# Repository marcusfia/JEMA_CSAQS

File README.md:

# **JEMA SD Project - Citizen Science Air Quality Sensor**
Sponsered by Dr. Jun Wang and the University of Iowa ARROMA Lab

This repository contains all source code used for the project.

If you would like to know more about the project software/hardware or access user guides, please visit the project wiki:

## [Project Wiki](https://github.com/marcusfia/JEMA_CSAQS/wiki)

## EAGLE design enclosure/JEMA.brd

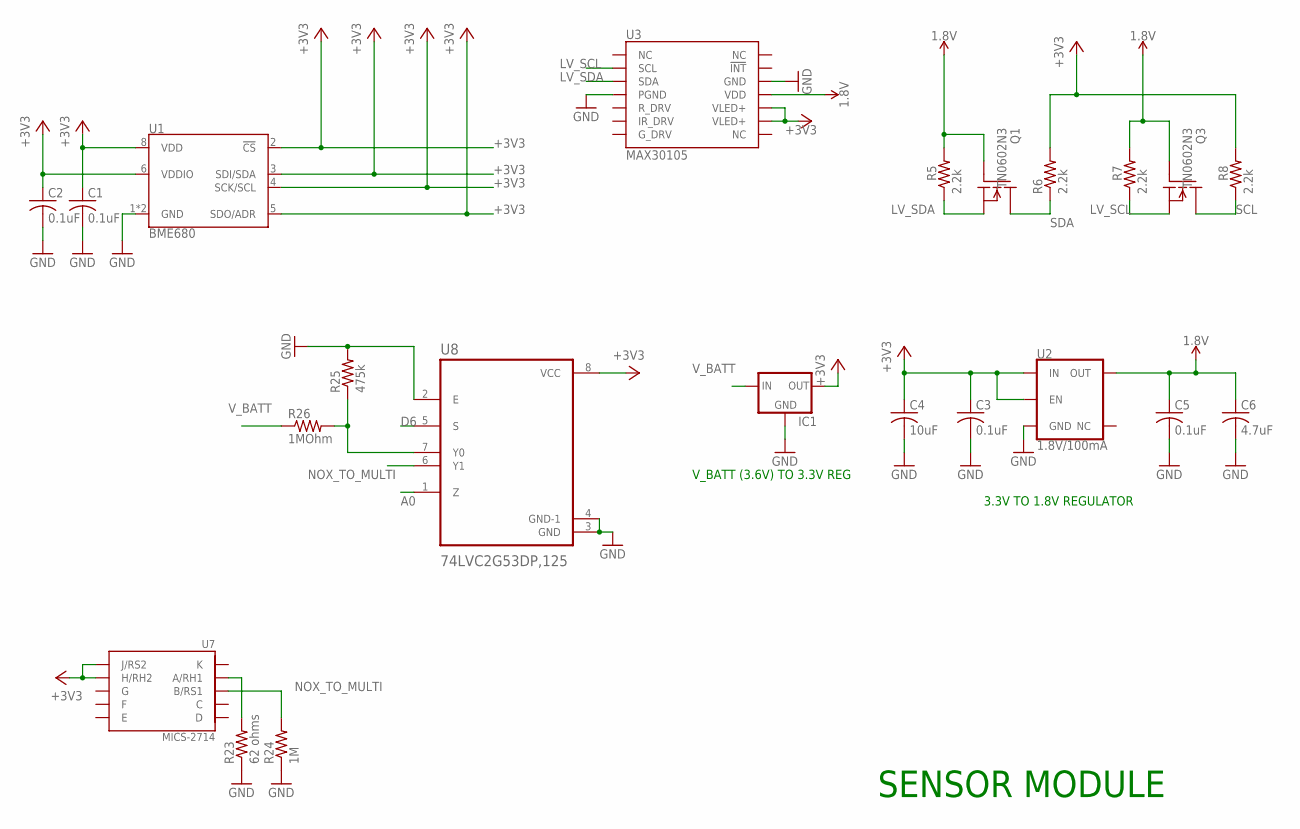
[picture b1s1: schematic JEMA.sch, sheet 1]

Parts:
C1, C2, C3, C5: 0.1uF; C0805
C4: 10uF; C0805
C6: 4.7uF; C0805
IC1: MCP1700TRI; TO92
Q1, Q3: TN0602N3; TO-92
R5, R6, R7, R8: 2.2k; R0805
R23: 62 ohms; M0805
R24: 1M; M0805
R25: 475k; M0805
R26: 1MOhm; M0805
U1: BME680; LGA3.0X3.0
U2: 1.8V/100mA; SC70
U3: MAX30105; OLGA-14
U7: MICS-2714; MICS-SMD10
U8: 74LVC2G53DP,125; SOP65P490X110-8N

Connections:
1.8V: C5.1, C6.1, Q1.2 (G), Q3.2 (G), R5.2, R7.2, U2.5 (OUT), U3.11 (VDD)
+3V3: C1.1, C2.1, C3.1, C4.1, IC1.3 (OUT), R6.2, R8.2, U1.2 (!CS), U1.3 (SDI/SDA), U1.4 (SCK/SCL), U1.5 (SDO/ADR), U1.6 (VDDIO), U1.8 (VDD), U2.1 (IN), U2.3 (EN), U3.9 (VLED+), U3.10 (VLED+), U7.H (H/RH2), U7.J (J/RS2), U8.8 (VCC); also elsewhere on the board
A0: U8.1 (Z); also elsewhere on the board
D6: U8.5 (S); also elsewhere on the board
GND: C1.2, C2.2, C3.2, C4.2, C5.2, C6.2, IC1.1 (GND), R23.1, R24.1, R25.2, U1.1 (GND), U1.7 (GND), U2.2 (GND), U3.4 (PGND), U3.12 (GND), U8.2 (E), U8.3 (GND), U8.4 (GND-1); also elsewhere on the board
LV_SCL: Q3.1 (S), R7.1, U3.2 (SCL)
LV_SDA: Q1.1 (S), R5.1, U3.3 (SDA)
unnamed: R25.1, R26.2, U8.7 (Y0)
unnamed: R23.2, U7.A (A/RH1)
NOX_TO_MULTI: R24.2, U7.B (B/RS1), U8.6 (Y1)
SCL: Q3.3 (D), R8.1; also elsewhere on the board
SDA: Q1.3 (D), R6.1; also elsewhere on the board
V_BATT: IC1.2 (IN), R26.1; also elsewhere on the board

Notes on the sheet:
V_BATT (3.6V) TO 3.3V REG
3.3V TO 1.8V REGULATOR
SENSOR MODULE

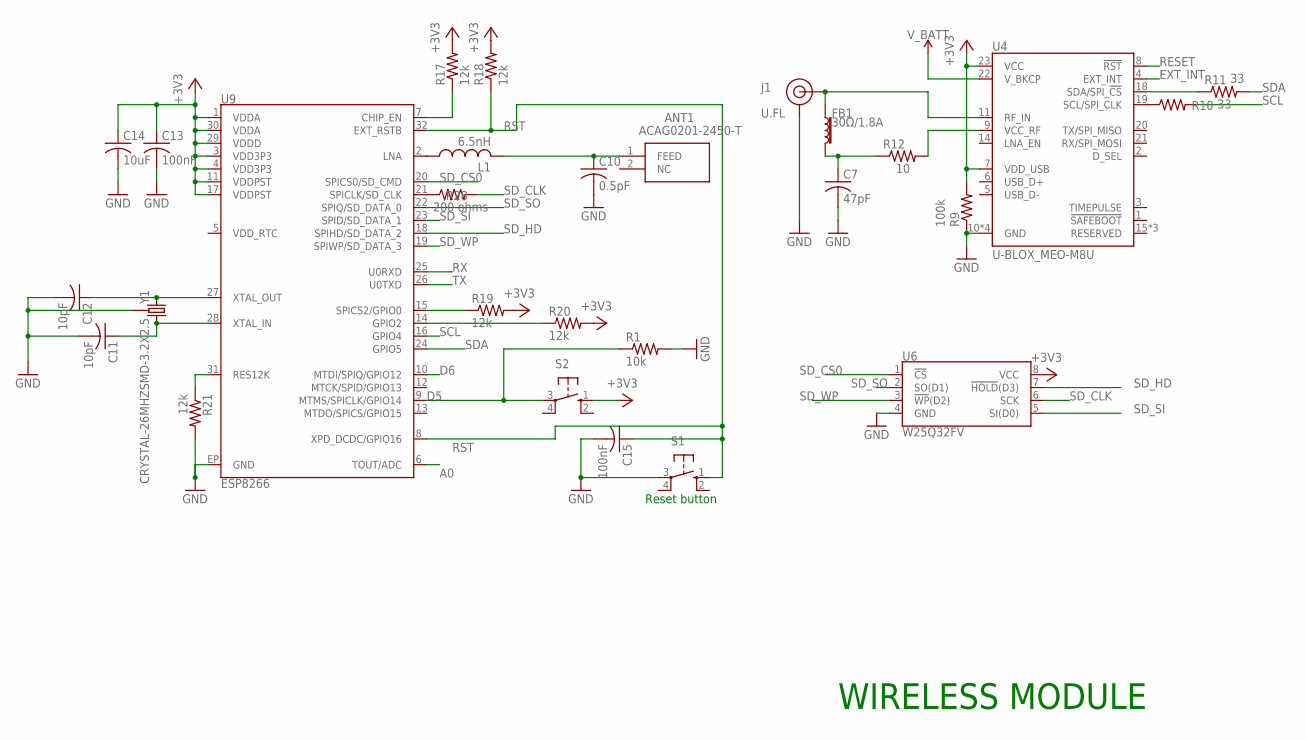
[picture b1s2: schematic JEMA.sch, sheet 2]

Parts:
ANT1: ACAG0201-2450-T; ANTC2012X70N
C7: 47pF; C0805
C10: 0.5pF; C0805
C11, C12: 10pF; C0805
C13, C15: 100nF; C0805
C14: 10uF; C0805
FB1: 30Ω/1.8A; 0603
J1: U.FL
L1: 6.5nH; L3225M
R1: 10k; R0805
R9: 100k; R0805
R10, R11: 33; R0805
R12: 10; R0805
R17, R18, R19, R20, R21: 12k; M0805
R28: 200 ohms; R0805
S1, S2: 10-XX; B3F-10XX
U4: U-BLOX_MEO-M8U; NEO-M9N/M8T/M8U
U6: W25Q32FV; SOIC-8
U9: ESP8266; QFN32-5X5MM
Y1: CRYSTAL-26MHZSMD-3.2X2.5; CRYSTAL-SMD-3.2X2.5MM

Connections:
+3V3: C13.1, C14.1, R9.2, R17.2, R18.2, R19.2, R20.2, S2.1 (S), U4.7 (VDD_USB), U4.23 (VCC), U6.8 (VCC), U9.1 (VDDA), U9.3 (VDD3P3), U9.4 (VDD3P3), U9.11 (VDDPST), U9.17 (VDDPST), U9.29 (VDDD), U9.30 (VDDA); also elsewhere on the board
A0: U9.6 (TOUT/ADC); also elsewhere on the board
D5: R1.1, S2.3, U9.9 (MTMS/SPICLK/GPIO14)
D6: U9.10 (MTDI/SPIQ/GPIO12); also elsewhere on the board
EXT_INT: U4.4 (EXT_INT)
GND: C7.2, C10.2, C11.2, C12.2, C13.2, C14.2, C15.2, J1.1 (GND), J1.2 (GND), R1.2, R9.1, R21.2, S1.3, U4.10 (GND), U4.12 (GND), U4.13 (GND), U4.24 (GND), U6.4 (GND), U9.EP (GND), Y1.2 (GND), Y1.4 (GND); also elsewhere on the board
unnamed: R10.1, U4.19 (SCL/SPI_CLK)
unnamed: R11.1, U4.18 (SDA/SPI_!CS!)
unnamed: C7.1, FB1.2, R12.1
unnamed: R12.2, U4.9 (VCC_RF)
unnamed: R17.1, U9.7 (CHIP_EN)
unnamed: L1.1, U9.2 (LNA)
unnamed: ANT1.1 (FEED), C10.1, L1.2
unnamed: R19.1, U9.15 (SPICS2/GPIO0)
unnamed: R20.1, U9.14 (GPIO2)
unnamed: R21.1, U9.31 (RES12K)
unnamed: C12.1, U9.27 (XTAL_OUT), Y1.1
unnamed: C11.1, U9.28 (XTAL_IN), Y1.3 (2)
unnamed: FB1.1, J1.FEED (SIGNAL), U4.11 (RF_IN)
unnamed: R28.1, U9.21 (SPICLK/SD_CLK)
RESET: U4.8 (!RST)
RST: C15.1, R18.1, S1.1 (S), U9.8 (XPD_DCDC/GPIO16), U9.32 (EXT_RSTB)
RX: U9.25 (U0RXD)
SCL: R10.2, U9.16 (GPIO4); also elsewhere on the board
SDA: R11.2, U9.24 (GPIO5); also elsewhere on the board
SD_CLK: R28.2, U6.6 (SCK)
SD_CS0: U6.1 (!CS!), U9.20 (SPICS0/SD_CMD)
SD_HD: U6.7 (!HOLD!(D3)), U9.18 (SPIHD/SD_DATA_2)
SD_SI: U6.5 (SI(D0)), U9.23 (SPID/SD_DATA_1)
SD_SO: U6.2 (SO(D1)), U9.22 (SPIQ/SD_DATA_0)
SD_WP: U6.3 (!WP!(D2)), U9.19 (SPIWP/SD_DATA_3)
TX: U9.26 (U0TXD)
V_BATT: U4.22 (V_BKCP); also elsewhere on the board

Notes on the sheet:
Reset button
WIRELESS MODULE

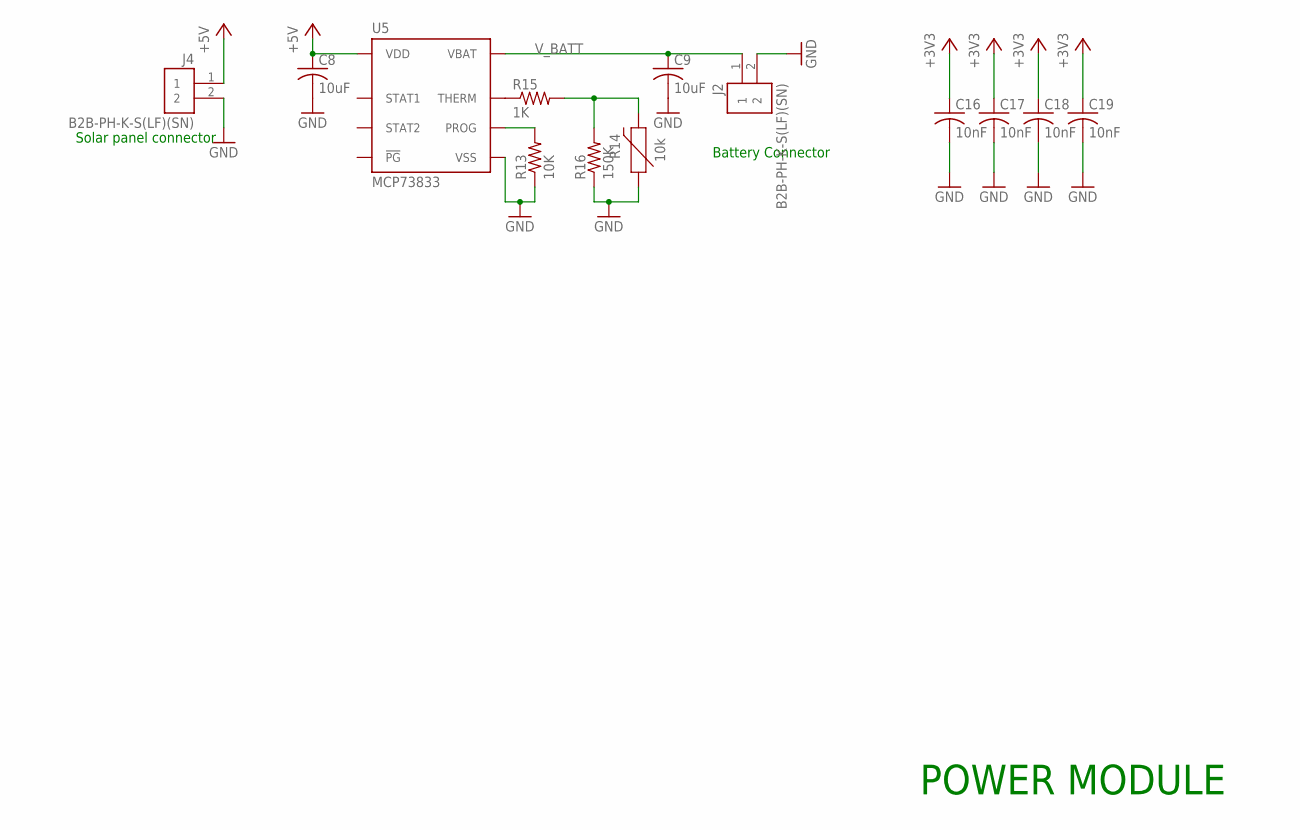
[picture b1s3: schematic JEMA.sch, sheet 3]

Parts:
C8, C9: 10uF; C0805
C16, C17, C18, C19: 10nF; C0805
J2, J4: B2B-PH-K-S(LF)(SN); JST_B2B-PH-K-S(LF)(SN)
R13: 10K; R0805
R14: 10k; 0603
R15: 1K; R0805
R16: 150K; R0805
U5: MCP73833; DFN-10

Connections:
+3V3: C16.1, C17.1, C18.1, C19.1; also elsewhere on the board
+5V: C8.1, J4.1, U5.P$1 (VDD), U5.P$2 (VDD)
GND: C8.2, C9.2, C16.2, C17.2, C18.2, C19.2, J2.2, J4.2, R13.1, R14.1, R16.1, U5.P$5 (VSS), U5.P$11 (VSS); also elsewhere on the board
unnamed: R13.2, U5.P$6 (PROG)
unnamed: R15.1, U5.P$8 (THERM)
unnamed: R14.2, R15.2, R16.2
V_BATT: C9.1, J2.1, U5.P$9 (VBAT), U5.P$10 (VBAT); also elsewhere on the board

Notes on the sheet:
POWER MODULE
Battery Connector
Solar panel connector

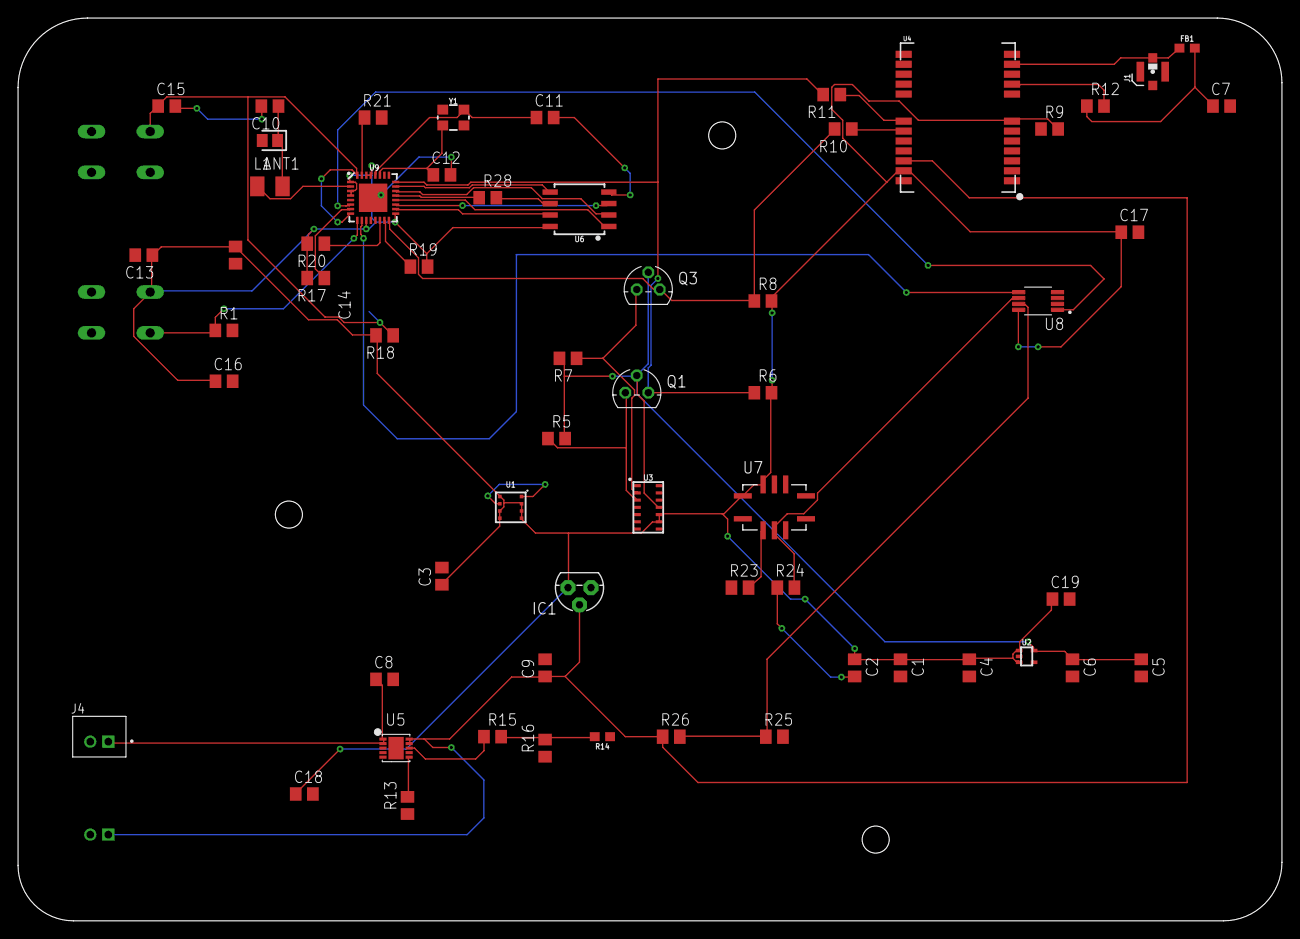
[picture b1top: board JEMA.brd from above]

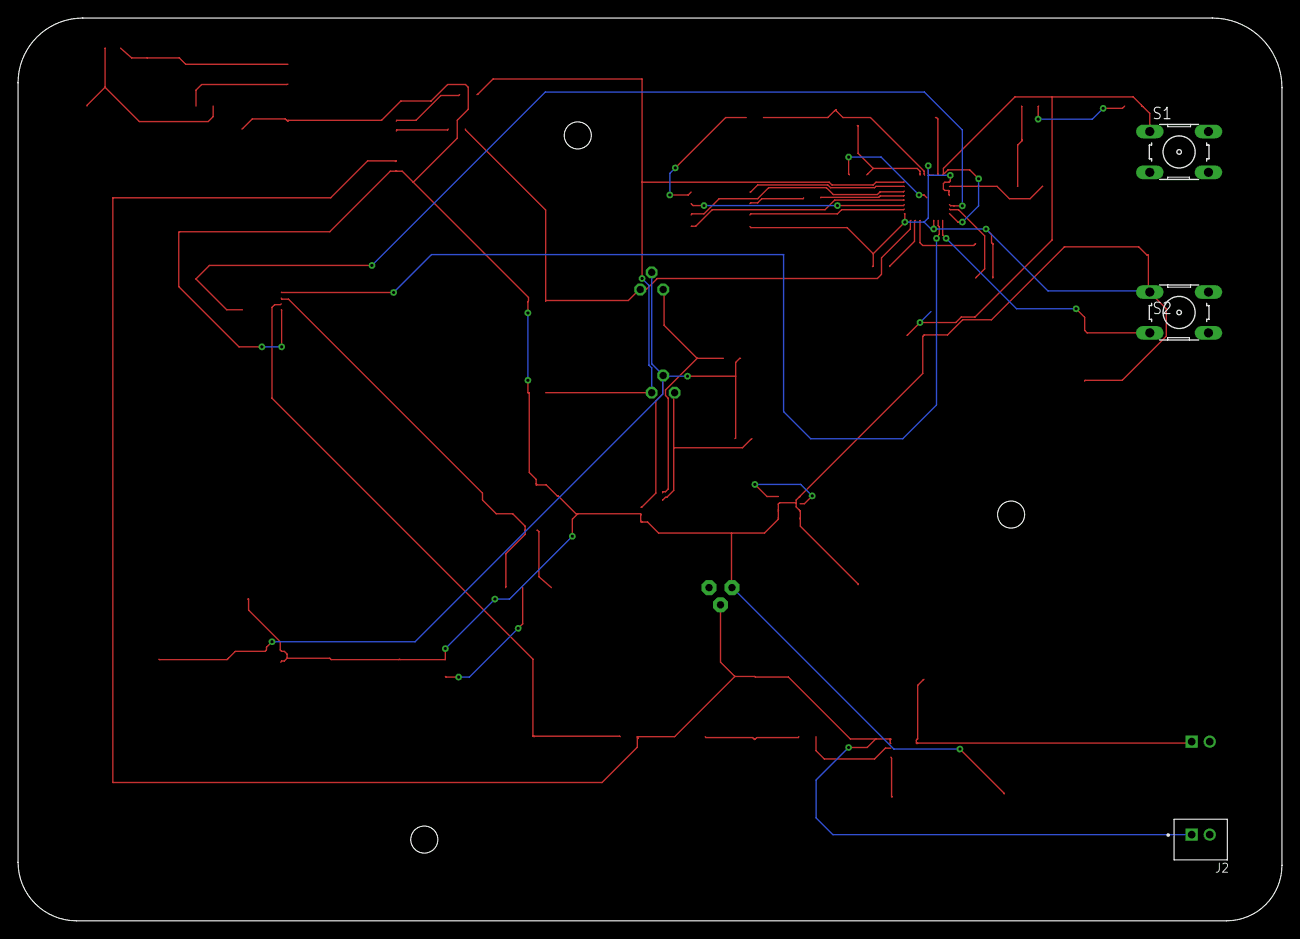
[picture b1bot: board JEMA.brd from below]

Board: 2 copper layers, 140.0 x 100.0 mm, 63 parts (3 on the bottom side), 39 nets.

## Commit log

2020-11-24 Add images for Hardware Wiki
2020-11-24 Add Hardware Wiki Images
2020-11-28 Committing Project Interactive Map Source Files
2020-12-12 Update JEMAdata.js
    Latest Frontend JS
2020-12-12 Update index.html
    Latest Frontend HTML
2020-12-14 Firmware source files

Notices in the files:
parts and their libraries:
SparkFun-Sensors: Licensing: Creative Commons ShareAlike 4.0 International - https://creativecommons.org/licenses/by-sa/4.0
